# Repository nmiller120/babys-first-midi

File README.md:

# Baby's First MIDI

A Fisher-Price piano hacked into a MIDI controller while preserving the toy's original functionality.

## Hardware

- Pimoroni Tiny 2350 (RP2350, 3.3 V logic)
- Fisher-Price Kick & Play-style piano
- Teenage Engineering EP-133 K.O. II as the initial MIDI target
- 3.5 mm TRS Type A MIDI output
- Two 10k potentiometers for octave/group and scale selection

## Current controller layout

### Piano keys

Five active-high digital inputs are mapped to the Fisher-Price piano keys:

| Tiny 2350 GPIO | Key |
| --- | --- |
| GP1 | Key 1 |
| GP2 | Key 2 |
| GP3 | Key 3 |
| GP4 | Key 4 |
| GP5 | Key 5 |

The GPIOs are configured as plain digital inputs with no internal pull-up or pull-down. A press sends MIDI Note On and releasing the key sends MIDI Note Off. Notes sustain for as long as a key is held, and multiple keys can be held simultaneously for polyphonic MIDI.

The key inputs use a 30 ms software debounce.

### A0 - octave / KO II group selector

A 10k potentiometer connected to A0 (GP26 / ADC0) selects the C-root octave:

| Setting | Root MIDI note | KO II group |
| --- | ---: | --- |
| C2 | 36 | A |
| C3 | 48 | B |
| C4 | 60 | C |
| C5 | 72 | D |

This uses the KO II's fixed MIDI note ranges to make the pot function as a physical A/B/C/D group selector.

### A1 - scale selector

A second 10k potentiometer connected to A1 (GP27 / ADC1) selects the interval mapping for the five keys:

| Setting | Five-key mapping |
| --- | --- |
| Chromatic | C, C#, D, D#, E |
| Major | C, D, E, F, G |
| Minor | C, D, Eb, F, G |
| Minor Pentatonic | C, Eb, F, G, Bb |
| Major Pentatonic | C, D, E, G, A |

The root is always C. The A0 octave selection is added to the interval pattern selected by A1 to produce the final MIDI note.

## Potentiometer calibration and filtering

Bench testing showed that both pots reach approximately 56,000 at the top of their useful ADC range rather than the full 65,535 returned by MicroPython's `read_u16()`.

The selector logic therefore uses a calibrated range:

    POT_ADC_MIN = 1000
    POT_ADC_MAX = 56000

Readings outside that range are clamped to the nearest endpoint. This provides usable dead zones at both physical ends of the pots and ensures the first and last selector positions are easy to reach.

To prevent ADC noise from causing selector chatter near a boundary, two filters are applied:

    POT_HYSTERESIS = 2000
    POT_DEBOUNCE_MS = 150

A pot must first move beyond the hysteresis boundary and then remain in the new discrete state for at least 150 ms before the selection is accepted.

The stable filtered selector state is also used when calculating MIDI notes, so debug output and actual MIDI behavior remain synchronized.

## MIDI output

Tiny 2350 UART0 TX is on GP0. MIDI serial runs at 31,250 baud.

The current 3.3 V MIDI transmitter breadboard is:

    Tiny 2350                     TRS Type A MIDI
    ---------                     ---------------
    3V3 --- 20R --- 10R -------- Ring
    GP0 ----------- 10R -------- Tip
    GND                         (not connected)
                                Sleeve: NC

The 20 ohm + 10 ohm series pair is a temporary 30 ohm approximation to the nominal 33 ohm transmitter resistor used in the 3.3 V MIDI circuit.

IMPORTANT: Verify wiring and polarity before connecting an instrument. The KO II uses TRS MIDI Type A.

## LED behavior

The Tiny 2350 onboard RGB LED is used as a MIDI activity indicator. It lights white while one or more notes are being held and turns off when the final active note is released.

## OLED readout

`main.py` shows the stable octave (C2-C5), KO II group (A-D), and full scale
name on the 128x64 SSD1306 OLED. It uses the same working SoftI2C setup as
Test003: SDA=GP6, SCL=GP7, VCC=3V3, GND=GND at 100 kHz. Keep the bundled
`Tests/ssd1306.py` installed as `/lib/ssd1306.py` on the Tiny.

The readout follows the filtered selections used for MIDI notes. Screen
updates occur on startup and selection changes, with 32-byte transfers
between key scans. A missing driver/display or I2C error disables the
readout for that run while the MIDI controller continues. Restart after
fixing the connection to enable the display again.

To deploy, open the updated `main.py` in Thonny and save it to the Tiny as
`/main.py`. Run it with F5; it will also run on subsequent board resets.

## Debug output

`main.py` has a hardcoded `DEBUG = False` flag near the top. Set it to `True`
to print startup selections, pot changes, key presses, and display diagnostics
to the USB MicroPython console. With `False`, application logging is silent;
MIDI UART messages and OLED updates still operate. MicroPython's own boot
banner and unhandled tracebacks are not controlled by this flag.

Changing the octave/group pot produces output similar to:

    OCTAVE | Octave: C4 | KO II Group: C | Root MIDI Note: 60

Changing the scale pot produces:

    SCALE  | Scale: Minor Pentatonic

Pressing a key reports the complete transformation:

    PRESS | Octave: C4 | KO II Group: C | Scale: Minor Pentatonic | MIDI Note: 67

This makes it possible to verify the pot selection, scale mapping, and resulting MIDI note from Thonny without relying solely on the KO II.

## Tests

The `Tests` directory contains development/bench scripts.

- `Test001.py` - initial UART MIDI and onboard LED test.
- `Test002.py` - periodically prints raw A0/A1 ADC readings and approximate voltages for potentiometer testing and calibration.
- `Test003.py` - SSD1306 128x64 I2C OLED hello-world test with a changing counter.

### Running Test003: OLED hello world

For the Hosyond 0.96-inch 128x64 SSD1306 I2C module (Amazon B09T6SJBV5):

| Display label | Tiny 2350 connection |
| --- | --- |
| GND | GND |
| VCC | 3V3 |
| SDA | GP6 |
| SCL | GP7 |

Wire with power disconnected and follow the printed labels, not the physical
header order. Power this module from 3V3 so its I2C pull-ups use 3.3 V logic.
These are the Tiny's numbered GPIO pins, not its separate Qw/ST connector.

1. Connect the Tiny in Thonny using its MicroPython interpreter. Stop the
   running controller with Stop/Restart or Ctrl+C.
2. Save the bundled `Tests/ssd1306.py` onto the Tiny as
   `/lib/ssd1306.py` (create the `lib` folder if needed).
3. Open `Tests/Test003.py` in Thonny and click Run. It can run from the
   computer; there is no need to replace the Tiny's `main.py`.
4. The console prints discovered I2C addresses. The screen should show
   **Hello world!**, **Baby's First MIDI - Test003** across two lines, the
   selected address, and a count updated approximately once per second.
5. Press Ctrl+C to stop; the script blanks the screen.

The test uses software I2C (SoftI2C) at 100 kHz and detects 0x3C or 0x3D (preferring 0x3C if
both respond). An address response alone does not identify the controller;
this test expects the SSD1306 module listed above. If nothing is detected,
check power and the SDA/SCL wiring. An import error means the driver has not
been saved to the Tiny's `/lib` folder. This is a standalone display test;
it does not run the piano/MIDI controller at the same time.

The bundled driver is an unmodified copy from
[MicroPython's SSD1306 driver](https://github.com/micropython/micropython-lib/blob/master/micropython/drivers/display/ssd1306/ssd1306.py),
Git blob `37ad682de94a11687c6afdac8cdc4dc88eb2b46c`.
Its license is included in `Tests/LICENSE-ssd1306.txt`.

## Development status

Current development branch: `feature/pot-scale-selection`.

Completed so far:

- Tiny 2350 MicroPython environment
- 31,250 baud MIDI UART output
- TRS Type A KO II MIDI communication
- Five debounced digital key inputs
- Sustained Note On / Note Off behavior
- Polyphonic key handling
- Onboard MIDI activity LED
- Four-position octave / KO II group selection
- Five-position scale selection
- Potentiometer ADC calibration
- Potentiometer hysteresis and time debounce
- Thonny debug logging

Next major hardware step is integrating the Tiny 2350 inputs with the Fisher-Price key signals while preserving the toy's original functionality.

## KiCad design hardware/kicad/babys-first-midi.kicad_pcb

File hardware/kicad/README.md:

# Baby's First MIDI — KiCad

KiCad hardware design files for Baby's First MIDI.

The Rev A prototype board is routed on two copper layers, with a filled backside
ground zone. Open `babys-first-midi.kicad_pro` so KiCad loads the project rules and
the `BFM` footprint library from `fp-lib-table`.

## DRC repair, 2026-09-11

Starting from placement-only commit `f590c33`, this revision:

- Moves the RJ45 back to the left side, inside the board outline and clear of the
  MIDI jack; moves the MIDI jack away from the lower-right mounting hole.
- Rotates the five MOSFET footprints to provide separate gate, drain and source
  escape paths, then routes all required connections and refills ground copper.
- Preserves every pad number and net assignment from the starting board.
- Fixes silkscreen overlaps, puts hidden values on F.Fab, and stores all seven
  prototype footprint definitions in the project-local `BFM.pretty` library.
- Saves explicit minimum rules: 0.25 mm copper clearance, 0.25 mm track width,
  0.50 mm copper-to-edge clearance, and 0.15 mm silkscreen clearance. Routes use
  0.30 mm tracks. No DRC exclusions or severity suppressions were added.

Validated with KiCad 10.0.6: **0 violations and 0 unconnected items**.
The machine-readable report is `validation/drc.json`. Reproduce from this folder:

```powershell
kicad-cli pcb drc --refill-zones --format json --exit-code-violations --output validation/drc.json babys-first-midi.kicad_pcb
```

This remains the prototype experiment described in the earlier design work:
the connector footprints remain project-specific draft geometries. The clean
result verifies board geometry and connectivity against the PCB net assignments;
it does not certify the remaining connector fit, enclosure fit or schematic parity.

## Populated 3D view

In PCB Editor, use View > 3D Viewer (Alt+3). Models are attached to the board
and to the project footprint library. Resistors and MOSFETs use KiCad's standard
STEP models; install the KiCad 10 3D model library if these do not appear.
The RJ45 uses a drawing-based model. The WH148 pots and Tiny
2350 now use the bundled drawing-based replacement models. Their geometry,
source drawings and remaining estimates are documented in
`3dmodels/MECHANICAL_NOTES.md`.

The WH148 replacement changes the old 3 mm pitch to 5 mm, with 1.3 mm holes.
Pots mount directly, shafts parallel to the board toward the top edge. The Tiny
footprint's mirrored banks are corrected and the module is rotated and moved
to put USB at the right edge. Routing and ground fill are regenerated while
preserving all numbered pad-to-net assignments. KiCad 10.0.6 DRC reports zero
violations and zero unconnected items; see `validation/drc.json`.

J2 is now the uxcell PJ-320A, using a Keebio STEP model and adapted footprint.
The user-supplied pinout maps MIDI_TIP to pin 4 and MIDI_RING to pin 3; pins 1
(sleeve, as before) and 2 (ring2) are unconnected. The mouth faces the right
edge. See `3dmodels/MECHANICAL_NOTES.md` for source attribution and geometry
limits. The replacement is rerouted and passes DRC with no unconnected items.

J1 now uses BFM:RJ45_FMHXG_AssumedPinout and a drawing-based model, facing the
left edge. The 8 signal holes, 2 locating holes and 2 shield holes follow the
user-supplied drawing. Sequential 1-8 numbering is an explicit prototype
assumption approved by the user, not a verified vendor pinout. Existing numbered
signal nets are preserved; shield pads are unconnected. See
`RJ45_CONTINUITY_CHECK.md` for the precise mapping to check when the parts arrive.
Rerouting and ground refill pass KiCad 10.0.6 DRC: zero violations and zero
unconnected items.

## 2N7000 input buffers

Q1-Q5 now use through-hole 2N7000 MOSFETs with the onsemi 2N7000TA
TO-92 pinout: 1=source (GND), 2=gate (input resistor), 3=drain (GPIO/pull-up).
Datasheet: https://www.onsemi.com/download/data-sheet/pdf/2n7000ta-d.pdf
The local BFM:TO-92_2N7000_SGD footprint derives from KiCad's
TO-92_Inline_Wide footprint. Its 2.54 mm hole spacing requires spreading the
leads; match the flat face to the fabrication outline. The 3D model is the
standard KiCad 10 TO-92_Inline_Wide STEP model.

PCB nets and schematic connections were checked against the previous design
by gate/drain/source function, including the required pin-number remap.
KiCad 10.0.6 DRC reports zero violations and zero unconnected items.
This verifies layout connectivity, not operation with the toy's unmeasured
signal voltage. Verify input switching on the assembled prototype.

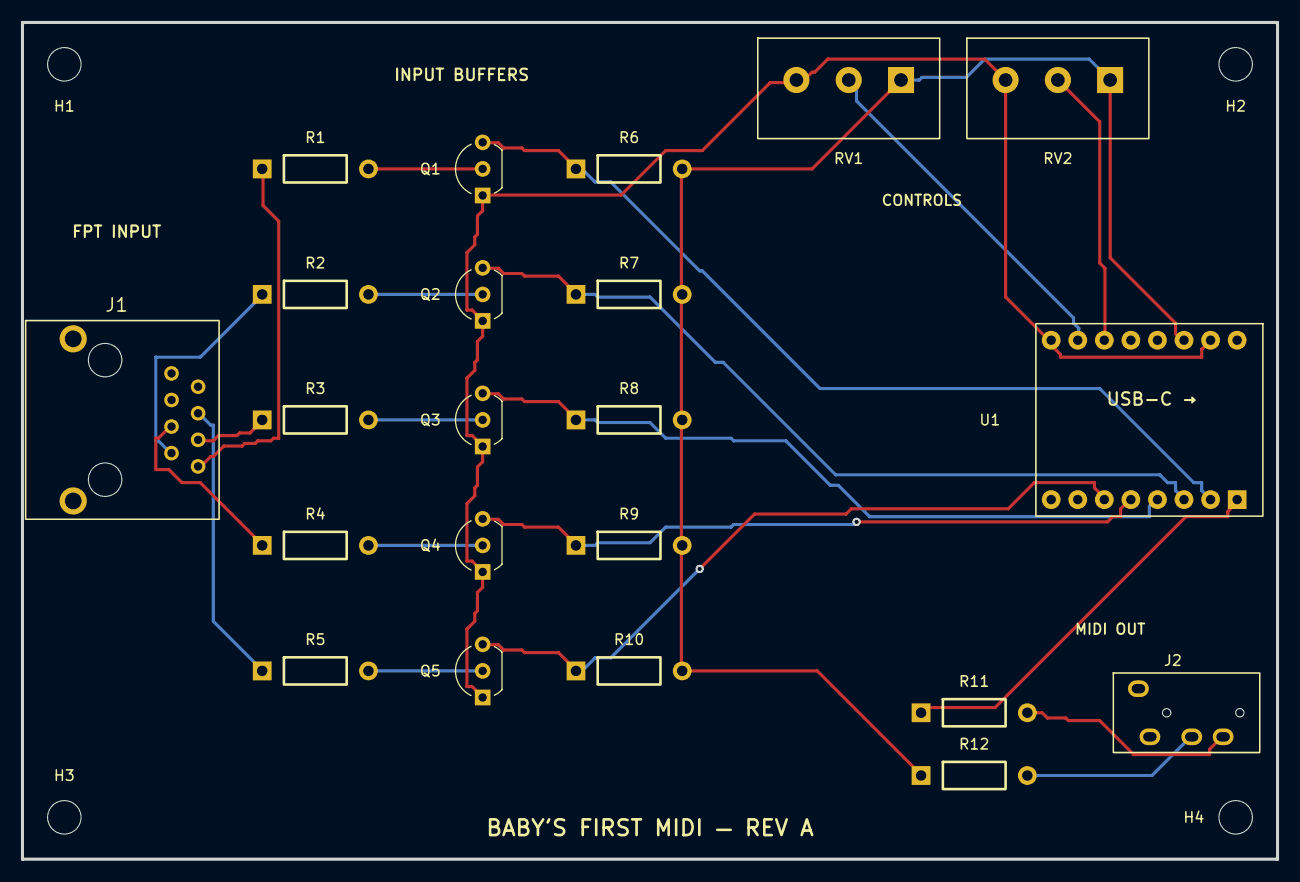
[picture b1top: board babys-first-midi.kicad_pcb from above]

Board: 2 copper layers, 120.0 x 80.0 mm, 26 parts (0 on the bottom side), 22 nets.

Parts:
H1, H2, H3, H4: MountingHole_3.2mm_M3
J1: RJ45NMCCFC-90D-10; RJ45_FMHXG_AssumedPinout
J2: PJ-320A; PJ320A_Uxcell_Horizontal
Q1, Q2, Q3, Q4, Q5: 2N7000; TO-92_2N7000_SGD
R1, R2, R3, R4, R5: 100k; Axial_10.16mm
R6, R7, R8, R9, R10: 10k; Axial_10.16mm
R11, R12: 33; Axial_10.16mm
RV1, RV2: 10k; WH148_Horizontal_P5.00mm
U1: BFM:Pimoroni_Tiny2350_2x8_Header; Pimoroni_Tiny2350_2x8_Header

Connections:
3V3: R6.2, R7.2, R8.2, R9.2, R10.2, R12.1, RV1.1, RV2.1, U1.11
ADC_OCTAVE: RV1.2, U1.15
ADC_SCALE: RV2.2, U1.14
FPT_C: J1.1, R1.1
FPT_D: J1.2, R2.1
FPT_E: J1.3, R3.1
FPT_F: J1.4, R4.1
FPT_G: J1.5, R5.1
GATE_C: Q1.2, R1.2
GATE_D: Q2.2, R2.2
GATE_E: Q3.2, R3.2
GATE_F: Q4.2, R4.2
GATE_G: Q5.2, R5.2
GND: Q1.1, Q2.1, Q3.1, Q4.1, Q5.1, RV1.3, RV2.3, U1.10, U1.16
KEY_C: Q1.3, R6.1, U1.2
KEY_D: Q2.3, R7.1, U1.3
KEY_E: Q3.3, R8.1, U1.4
KEY_F: Q4.3, R9.1, U1.5
KEY_G: Q5.3, R10.1, U1.6
MIDI_RING: J2.3, R12.2
MIDI_TIP: J2.4, R11.2
MIDI_TX: R11.1, U1.1
